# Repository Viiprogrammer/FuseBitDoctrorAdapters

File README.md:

# FuseBitDoctrorAdapters
 Adapters for AtmegaFusebitDoctor

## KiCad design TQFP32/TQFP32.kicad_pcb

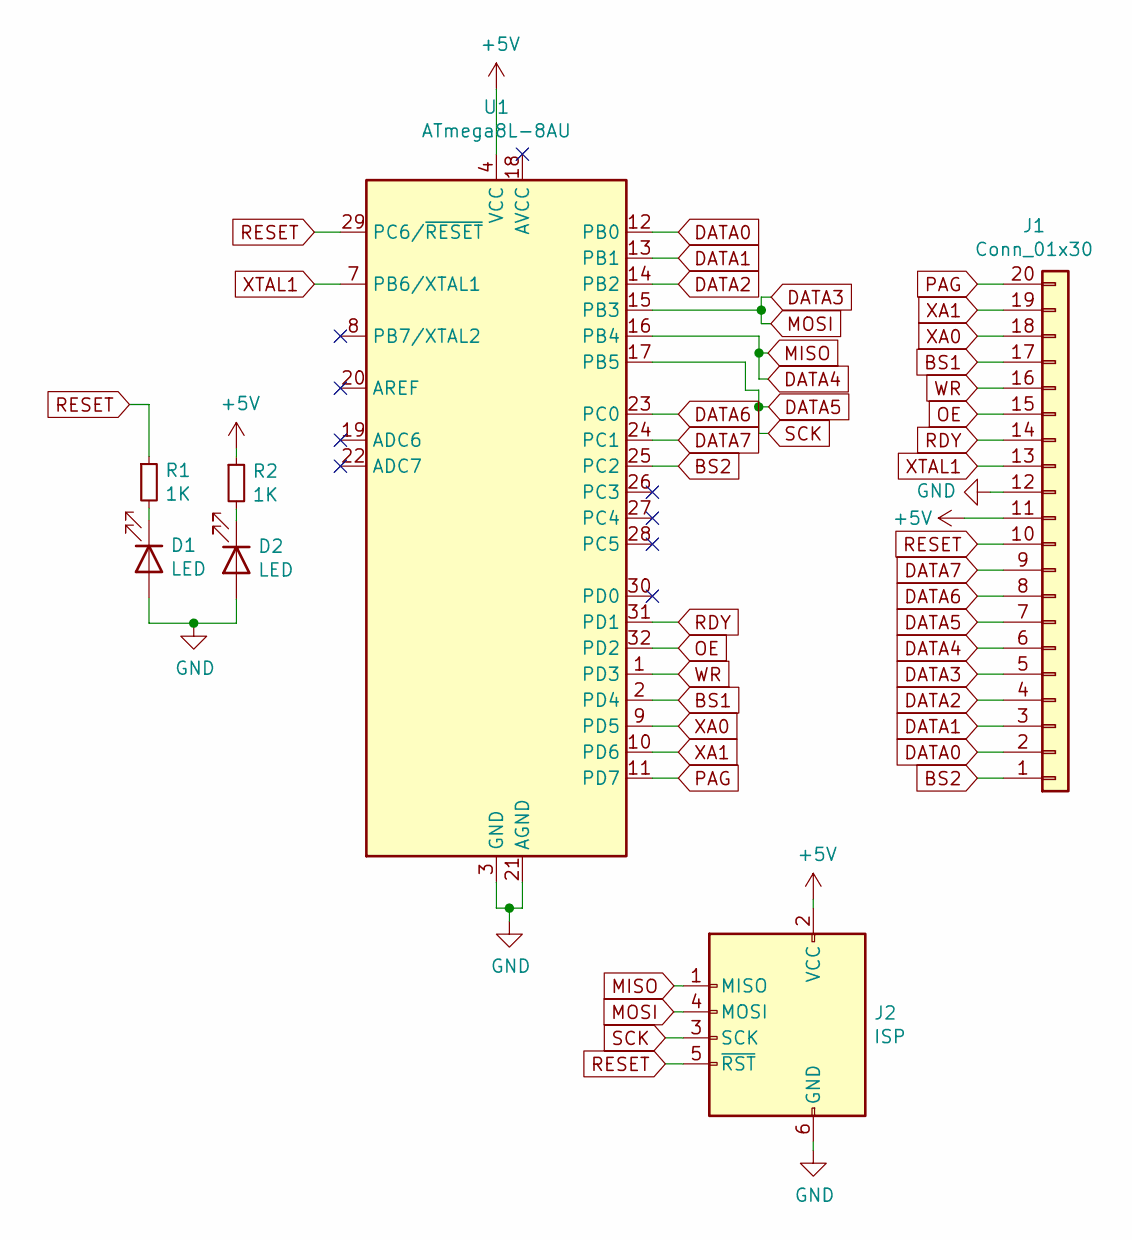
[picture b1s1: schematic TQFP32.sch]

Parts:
D1, D2: LED; LED_0805_2012Metric_Pad1.15x1.40mm_HandSolder
J1: Conn_01x30; PinSocket_1x20_P2.54mm_Horizontal
J2: ISP; PinHeader_2x03_P2.54mm_Vertical
R1, R2: 1К; R_0805_2012Metric_Pad1.20x1.40mm_HandSolder
U1: ATmega8L-8AU; TQFP-32_7x7mm_P0.8mm

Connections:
+5V: J1.11, J2.2 (VCC), R2.1, U1.4 (VCC), U1.6 (VCC)
BS1: J1.17, U1.2 (PD4)
BS2: J1.1, U1.25 (PC2)
DATA0: J1.2, U1.12 (PB0)
DATA1: J1.3, U1.13 (PB1)
DATA2: J1.4, U1.14 (PB2)
DATA3: J1.5, J2.4 (MOSI), U1.15 (PB3)
DATA4: J1.6, J2.1 (MISO), U1.16 (PB4)
DATA5: J1.7, J2.3 (SCK), U1.17 (PB5)
DATA6: J1.8, U1.23 (PC0)
DATA7: J1.9, U1.24 (PC1)
GND: D1.2 (A), D2.2 (A), J1.12, J2.6 (GND), U1.3 (GND), U1.5 (GND), U1.21 (AGND)
unnamed: D1.1 (K), R1.2
unnamed: D2.1 (K), R2.2
OE: J1.15, U1.32 (PD2)
PAG: J1.20, U1.11 (PD7)
RDY: J1.14, U1.31 (PD1)
RESET: J1.10, J2.5 (~RST), R1.1, U1.29 (PC6/~RESET)
WR: J1.16, U1.1 (PD3)
XA0: J1.18, U1.9 (PD5)
XA1: J1.19, U1.10 (PD6)
XTAL1: J1.13, U1.7 (PB6/XTAL1)

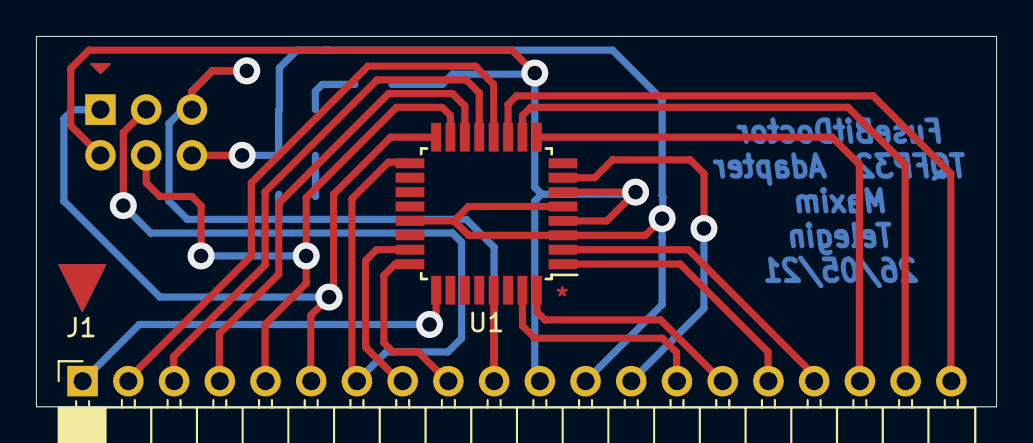
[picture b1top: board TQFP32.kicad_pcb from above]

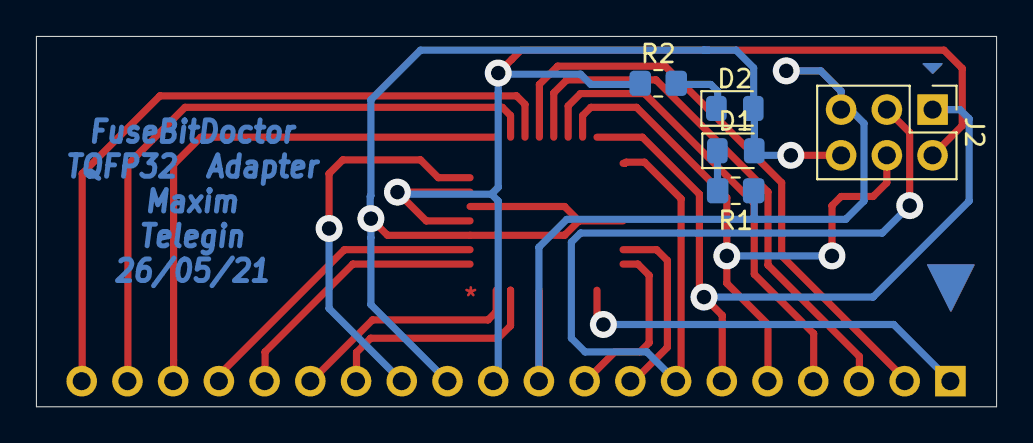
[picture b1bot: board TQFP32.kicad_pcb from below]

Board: 2 copper layers, 53.3 x 20.6 mm, 7 parts (5 on the bottom side), 22 nets.

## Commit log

2021-05-26 Added TQFP32 adapter
2021-05-28 Added ISP6 & LED for RESET & LED for POWER
